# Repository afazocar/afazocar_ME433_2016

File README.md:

#Alejandro F. Azocar
20160331

ME 433- Advanced Mechatronics Github Repository

Used to keep track of homework and projects.

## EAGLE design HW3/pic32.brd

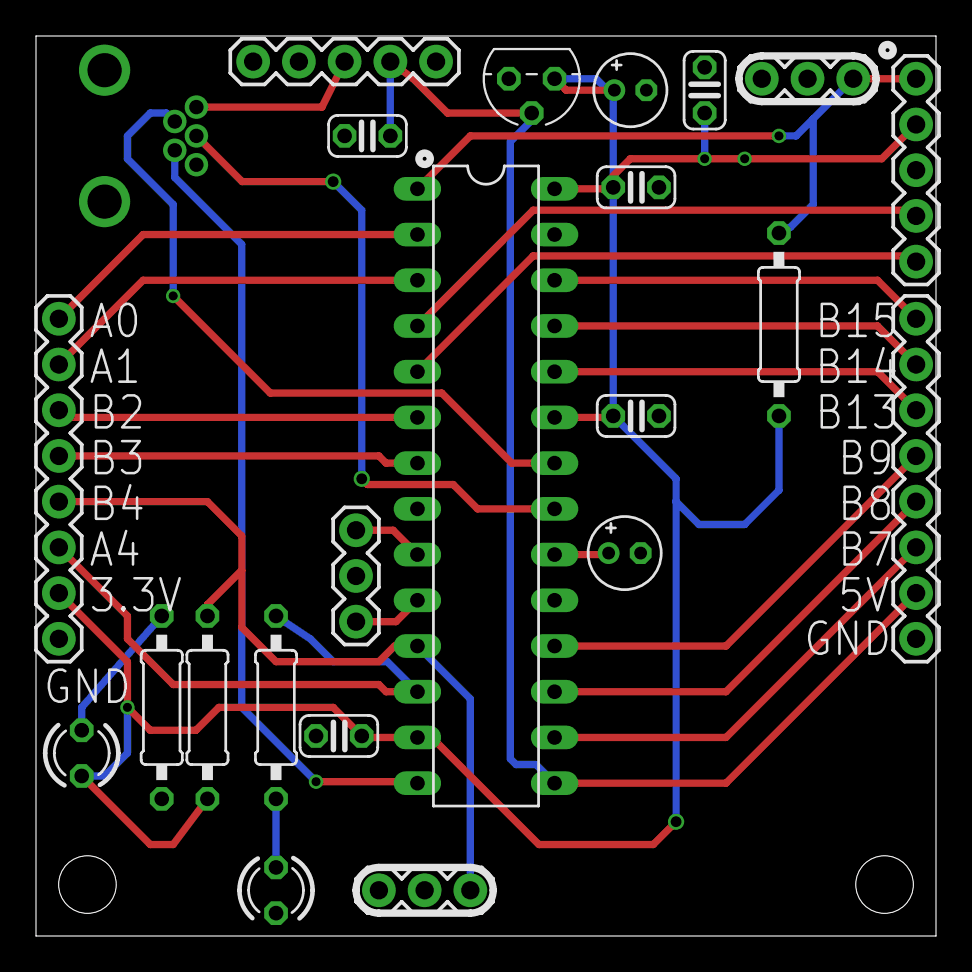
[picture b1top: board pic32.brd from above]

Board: 2 copper layers, 50.0 x 50.0 mm, 23 parts (0 on the bottom side), 27 nets.

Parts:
C1, C2, C4, C6, C7: 0.1uF; C025-024X044
C3, C5: 10uF; E1,8-4
J1: USB-MB-H
J2: ICSP; 1X05
J3: RESET; 1X03
J4: USER; 1X03
J5: 8MHz; 1X03
J6, J7: 1X08_ROUND
LED2, LED3: LED3MM
R1, R3: 330; 0207/10
R2, R4: 10k; 0207/10
SWITCH: 1X05
U$1: PIC32MX250F128B; DIL28-3
U$2: MCP1702; TO92

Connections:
+3V3: C2.1, C3.+, C4.2, C6.1, C7.1, J2.2, J6.2, LED3.A, R2.2, R4.2, U$1.13, U$1.23, U$1.28, U$2.3
+5V: C1.1, J7.2, SWITCH.4, U$1.15, U$2.2
A0: J6.8, U$1.2
A1: J6.7, U$1.3
A4: J6.3, R3.2, U$1.12
B2: J6.6, U$1.6
B3: J6.5, U$1.7
B4: J4.3, J6.4, R4.1, U$1.11
B7: J7.3, U$1.16
B8: J7.4, U$1.17
B9: J7.5, U$1.18
B13: J7.6, U$1.24
B14: J7.7, U$1.25
B15: J7.8, U$1.26
D+: J1.D+, U$1.21
D-: J1.D-, U$1.22
GND: C1.2, C2.2, C3.-, C4.1, C5.-, C6.2, C7.2, J1.GND, J2.3, J3.1, J4.1, J5.2, J6.1, J7.1, LED2.K, R1.1, U$1.8, U$1.19, U$1.27, U$2.1
MCLR: J2.1, J3.3, R2.1, U$1.1
unnamed: LED3.K, R1.2
unnamed: J1.VBUS, SWITCH.3
unnamed: C5.+, U$1.20
unnamed: LED2.A, R3.1
OSC1: J5.3, U$1.9
OSC2: J5.1, U$1.10
PGEC1: J2.5, U$1.5
PGED1: J2.4, U$1.4
USBID: J1.ID, U$1.14

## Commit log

2016-04-01 My first commit!
2016-04-01 More description
2016-04-03 3.3 V Oscillations without capacitors
2016-04-03 3.3 V Flat with capacitors
2016-04-03 Breadboard without capacitors
2016-04-03 Breadboard with capacitors
2016-04-03 3.3 V Flat with PIC32
2016-04-03 Breadboard with PIC32
2016-04-03 3.3 V FINAL DESIGN
2016-04-03 Breadboard FINAL DESIGN
2016-04-04 Created new project
2016-04-05 Defined the #PRAGMA commands
2016-04-05 Defined push-button as input, LED as output
2016-04-05 Toggle LED at 1000 Hz, turn off while button is pressed
2016-04-05 Breadboard with LED on (button not pressed)
2016-04-05 Breadboard with LED off (button pressed)
2016-04-05 Sketch of circuit
2016-04-10 Creating EAGLE library, includes voltage regulated & PIC32
2016-04-10 Began schematic. Includes USB, MCP1702, & ICSP
2016-04-10 Added buttons, LED, oscillator, etc
2016-04-10 Finished first draft of schematic
2016-04-14 Ready to be checked before order
2016-05-05 Cleaned up code
2016-05-05 SPI and I2C communication
2016-05-11 Picture of LED on when I2C button is pressed
2016-05-11 Turn on LED if WHO_AM_I is correct
2016-05-13 Misc
2016-05-13 LCD prints "Hello World 1337!"
2016-05-13 LCD printing message
2016-05-21 Android Hello World with slider
2016-05-21 Android line COM finder
2016-05-21 Added slider to change which row is tracked
2016-05-21 Added slider to change black threshold
2016-05-21 Initial wheel hub design- need to measure motor adapter
2016-05-24 Wheel hub with correct motor adapter size
2016-05-24 Increased length of motor adapter
2016-05-26 Added flash to camera app
2016-05-29 Added rocket countdown with delay
2016-05-29 Accidentally Deleted this...
2016-05-29 Revert "Added rocket countdown with delay"
    This reverts commit e427e452390207448957e89b9ea6eb5d199716d3.
2016-05-29 Revert "LCD prints "Hello World 1337!""
    This reverts commit 87ebdc3a3ca9cc0fd0896af753e4d83a6c2d4cfa.
2016-05-31 Recovered HW 5 (accidentally deleted before)
2016-06-02 Renamed folders
2016-06-03 PIC CDC returns integers
2016-06-03 Android CDC works
2016-06-03 Screenshots of seekbar and PIC return value
2016-06-03 Video of LED controlled by Seekbar PWM
2016-06-10 HW 4 and 6 complete
2016-06-10 Picture of wheel
2016-06-10 Screenshot of hello world
2016-06-10 Box CAD and pictures
2016-06-10 Final Android Code for Tech Cup
2016-06-10 Final PIC32 code for Tech Cup
2016-06-10 Final tech cup stuff
2016-06-10 Basic mouse program
2016-06-10 Updated mouse code
2016-06-10 Modified code
